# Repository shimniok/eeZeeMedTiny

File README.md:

# eeZeeMedTiny
A breadboard breakout / target board for ATtiny84 family

The smallest breakout & target board for the 14-pin ATtiny84, including AVR ISP header, reset switch and pull-up resistor,
and bypass caps. Step up to an ATtiny84 for more power and 6 more pins.

Easy to breadboard, prototype and program ATtiny84 with eeZee Medium Tiny. 

[For sale on Tindie.com](https://www.tindie.com/products/bot_thoughts/attiny84-development-board/)

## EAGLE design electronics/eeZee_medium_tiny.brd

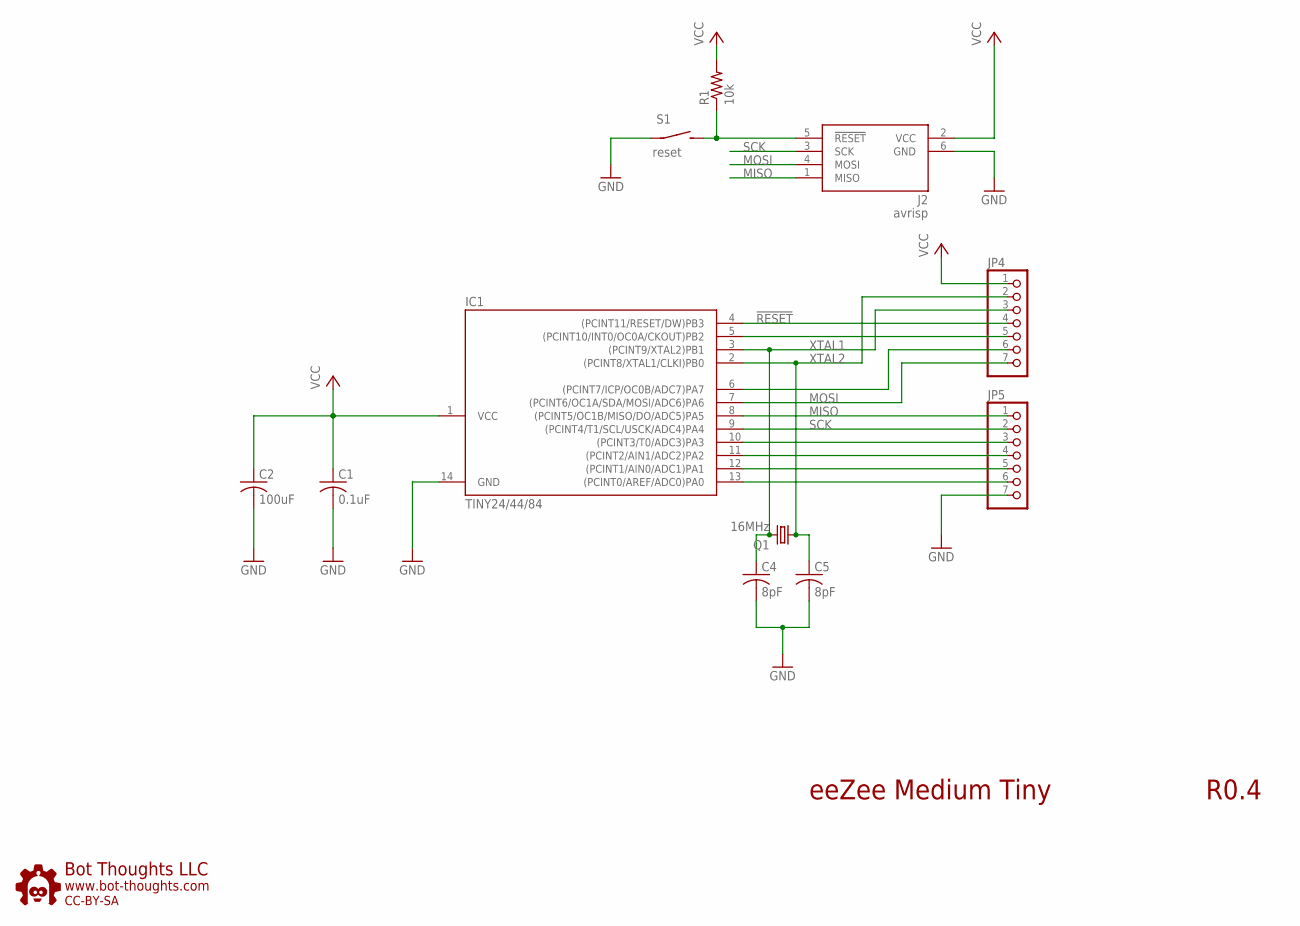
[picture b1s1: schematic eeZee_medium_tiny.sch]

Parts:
C1: 0.1uF; C0603; PARTNO 0603YC104KAT2A
C2: 100uF; C1206; PARTNO MCTT21X106M6R3CT
C4, C5: 8pF; C0603; PARTNO 0603YC104KAT2A
IC1: TINY24/44/84; DIL14
J2: avrisp; CON6P2R
JP4, JP5: PINHD-1X07_2.54-S; 1X07-S
Q1: 16MHz; NDK_2PAD_5X3
R1: 10k; R0603; PARTNO ERJ-3GEYJ103V
S1: reset; 6MMTACTILE_RECT
U$1: BTLOGO-LOGO-SM; BTLOGOS

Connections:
!RESET: IC1.4 ((PCINT11/RESET/DW)PB3), J2.5 (!RESET), JP4.4, R1.1, S1.P$2 (S)
GND: C1.2, C2.2, C4.2, C5.2, IC1.14 (GND), J2.6 (GND), JP5.7, S1.P$1
MISO: IC1.8 ((PCINT5/OC1B/MISO/DO/ADC5)PA5), J2.1 (MISO), JP5.1
MOSI: IC1.7 ((PCINT6/OC1A/SDA/MOSI/ADC6)PA6), J2.4 (MOSI), JP4.7
unnamed: IC1.5 ((PCINT10/INT0/OC0A/CKOUT)PB2), JP4.5
unnamed: IC1.6 ((PCINT7/ICP/OC0B/ADC7)PA7), JP4.6
unnamed: IC1.10 ((PCINT3/T0/ADC3)PA3), JP5.3
unnamed: IC1.11 ((PCINT2/AIN1/ADC2)PA2), JP5.4
unnamed: IC1.12 ((PCINT1/AIN0/ADC1)PA1), JP5.5
unnamed: IC1.13 ((PCINT0/AREF/ADC0)PA0), JP5.6
SCK: IC1.9 ((PCINT4/T1/SCL/USCK/ADC4)PA4), J2.3 (SCK), JP5.2
VCC: C1.1, C2.1, IC1.1 (VCC), J2.2 (VCC), JP4.1, R1.2
XTAL1: C5.1, IC1.2 ((PCINT8/XTAL1/CLKI)PB0), JP4.2, Q1.P$1 (1)
XTAL2: C4.1, IC1.3 ((PCINT9/XTAL2)PB1), JP4.3, Q1.P$2 (2)

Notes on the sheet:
eeZee Medium Tiny
R0.4

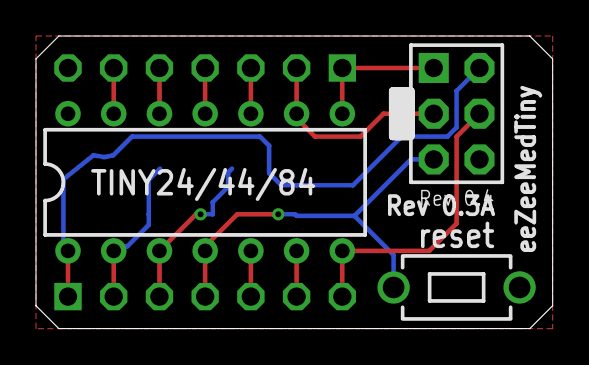
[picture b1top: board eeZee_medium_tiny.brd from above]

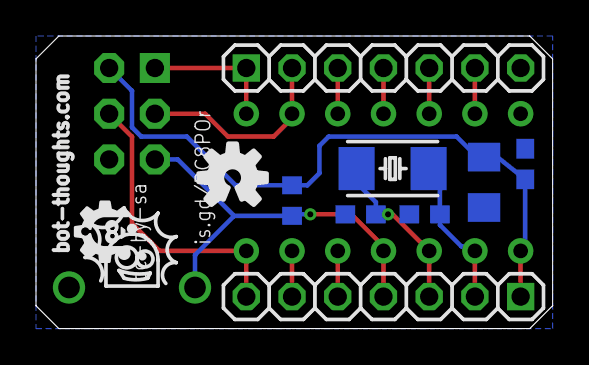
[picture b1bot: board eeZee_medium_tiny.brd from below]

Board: 2 copper layers, 28.7 x 16.3 mm, 12 parts (9 on the bottom side), 14 nets.

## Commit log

2013-01-08 Initial revision
2013-01-08 Renamed files
2013-01-08 Minor board tweaks
2013-08-06 Rev 0.2 as ordered, mitered corners, flipped tantalum and added polarity silk screen, changed location of caps/crystals for easier assembly, shrunk board size.
2013-11-10 Created electronics and firmware directories so I could host example code.
2013-11-10 Adding firmware examples
2013-11-10 Updated comments
2014-04-15 Revised pads for IC, revised 10uF filtering cap footprint to 1206.
2014-04-15 Removed extraneous silkscreen
2014-10-17 Changed spacing to 10mil/8mil, relocated too-close traces, relocated via
2015-05-04 revised licenses
2015-07-31 Added assembly instructions
2022-03-07 update logo, silk, add help url
2022-03-07 updated gerbers, zip
2022-03-07 added documentation source images
2022-03-07 added gitignore
2022-03-07 Updated readme with link to store and description
2022-03-07 added pics to readme
2022-03-07 fixed pic #2 in readme
2022-03-07 switched pics for better ones

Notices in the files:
electronics/eeZee_medium_tiny.brd:
cc-by-sa
